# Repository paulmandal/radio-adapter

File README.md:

# Radio Adapter Board
Adapter board to connect a Yaesu VX-8DR with a Garmin GPSmap64 and various .mil microphones

# Requirements

- [Arduino](https://www.arduino.cc/en/Main/Software)
- [Eagle](https://www.autodesk.com/products/eagle/free-download)
- You must copy `ucontroller-code/platform.local.txt` to your `$ARDUINO_HOME/hardware/arduino/avr` directory to enable printf formatting of floats

# Table of Contents

| Directory | Contents |
|---|----|
| ucontroller-code | Arduino sketch to translate Garmin GPS NMEA sentences into the fixed-length that the Yaesu VX-8DR expects |
| circuit-board | Eagle circuit diagrams and PCB layouts for the adapter board |
| dev-tools | Various Python scripts that were useful during development |

# Important Note

The ATmega328p chips I got needed to have their fuses set, there is a script `set-fuses.sh` that will do this for you.  You may need to change the programmer from `usbtiny` to whatever you have on hand.

# References

This project borrows heavily from these sources:

[Reverse Engineering the Yaesu VX-8DR GPS Interface](http://lingnik.com/2013/02/09/reverse-engineering-yaesu-vx-8dr-gps-interface.html)

[Dynamic microphone to electret microphone input](http://www.epanorama.net/circuits/dynamic_to_electretinput.html)

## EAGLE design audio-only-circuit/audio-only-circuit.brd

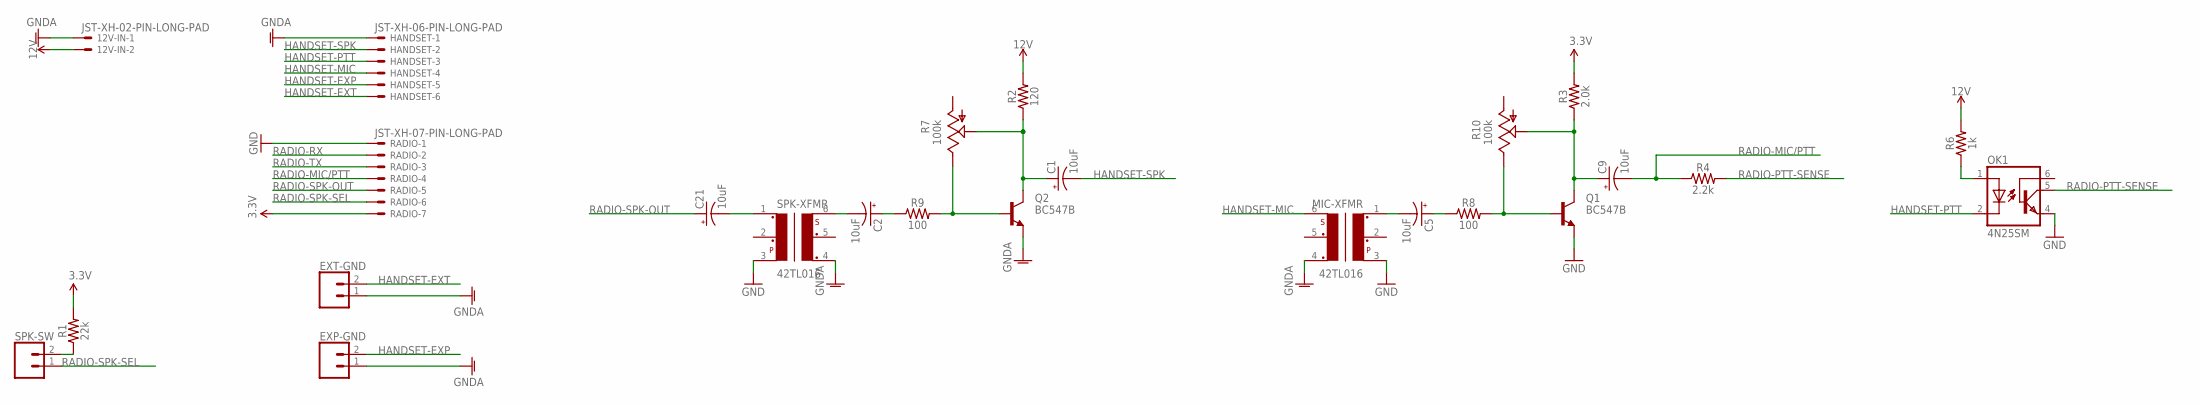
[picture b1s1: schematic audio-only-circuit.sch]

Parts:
12V-IN: JST-XH-02-PIN-LONG-PAD; JST-XH-02-PACKAGE-LONG-PAD
C1, C2, C5, C9, C21: 10uF; E2,5-5
EXP-GND: CONN_02; 1X02
EXT-GND: CONN_02; 1X02
HANDSET: JST-XH-06-PIN-LONG-PAD; JST-XH-06-PACKAGE-LONG-PAD
MIC-XFMR: 42TL016; 42TL
OK1: 4N25SM; DIL6-SMD
Q1, Q2: BC547B; TO92
R1: 22k; 0603
R2: 120; 0603
R3: 2.0k; 0603
R4: 2.2k; 0603
R6: 1k; 0603
R7, R10: 100k; S64W
R8, R9: 100; 0603
RADIO: JST-XH-07-PIN-LONG-PAD; JST-XH-07-PACKAGE-LONG-PAD
SPK-SW: CONN_02; 1X02
SPK-XFMR: 42TL016; 42TL

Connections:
3.3V: R1.2, R3.2, RADIO.7
12V: 12V-IN.2, R2.2, R6.2
GND: MIC-XFMR.3, OK1.4 (EMI), Q1.1 (E), RADIO.1, SPK-XFMR.3
GNDA: 12V-IN.1, EXP-GND.1, EXT-GND.1, HANDSET.1, MIC-XFMR.4, Q2.1 (E), SPK-XFMR.4
HANDSET-EXP: EXP-GND.2, HANDSET.5
HANDSET-EXT: EXT-GND.2, HANDSET.6
HANDSET-MIC: HANDSET.4, MIC-XFMR.6
HANDSET-PTT: HANDSET.3, OK1.2 (C)
HANDSET-SPK: C1.-, HANDSET.2
unnamed: C2.-, SPK-XFMR.6
unnamed: C9.+, Q1.3 (C), R3.1, R10.S
unnamed: Q1.2 (B), R8.2, R10.E
unnamed: Q2.2 (B), R7.E, R9.2
unnamed: C21.-, SPK-XFMR.1
unnamed: C5.-, MIC-XFMR.1
unnamed: C5.+, R8.1
unnamed: OK1.1 (A), R6.1
unnamed: C2.+, R9.1
unnamed: R1.1, SPK-SW.2
RADIO-MIC/PTT: C9.-, R4.1, RADIO.4
RADIO-PTT-SENSE: OK1.5 (COL), R4.2
RADIO-RX: RADIO.2
RADIO-SPK-OUT: C21.+, RADIO.5
RADIO-SPK-SEL: RADIO.6, SPK-SW.1
RADIO-TX: RADIO.3
SPKAMP: C1.+, Q2.3 (C), R2.1, R7.S

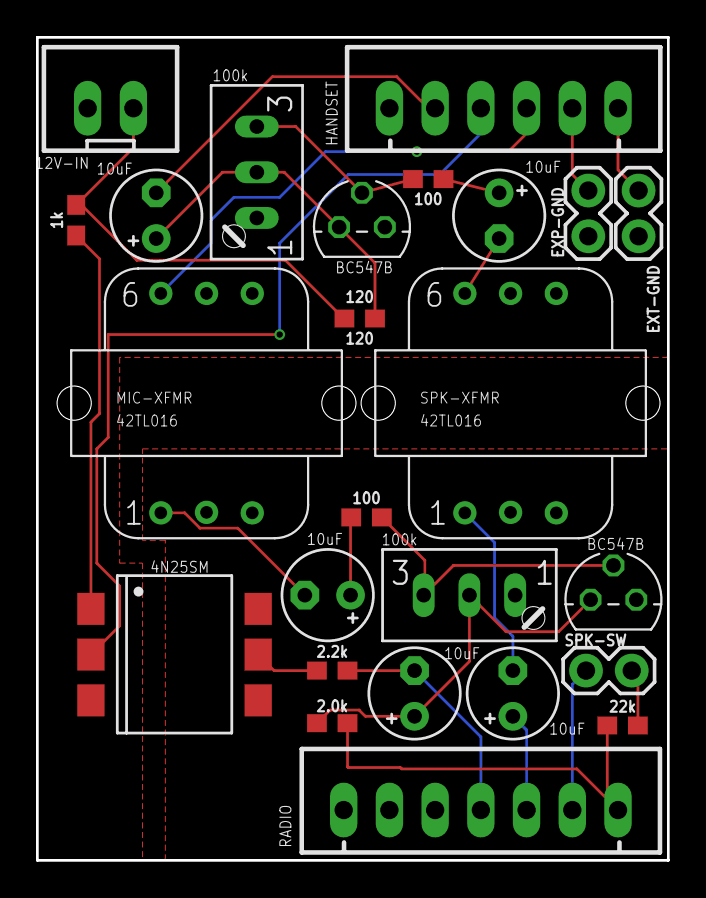
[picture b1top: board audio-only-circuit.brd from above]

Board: 2 copper layers, 35.1 x 45.7 mm, 25 parts (0 on the bottom side), 24 nets.

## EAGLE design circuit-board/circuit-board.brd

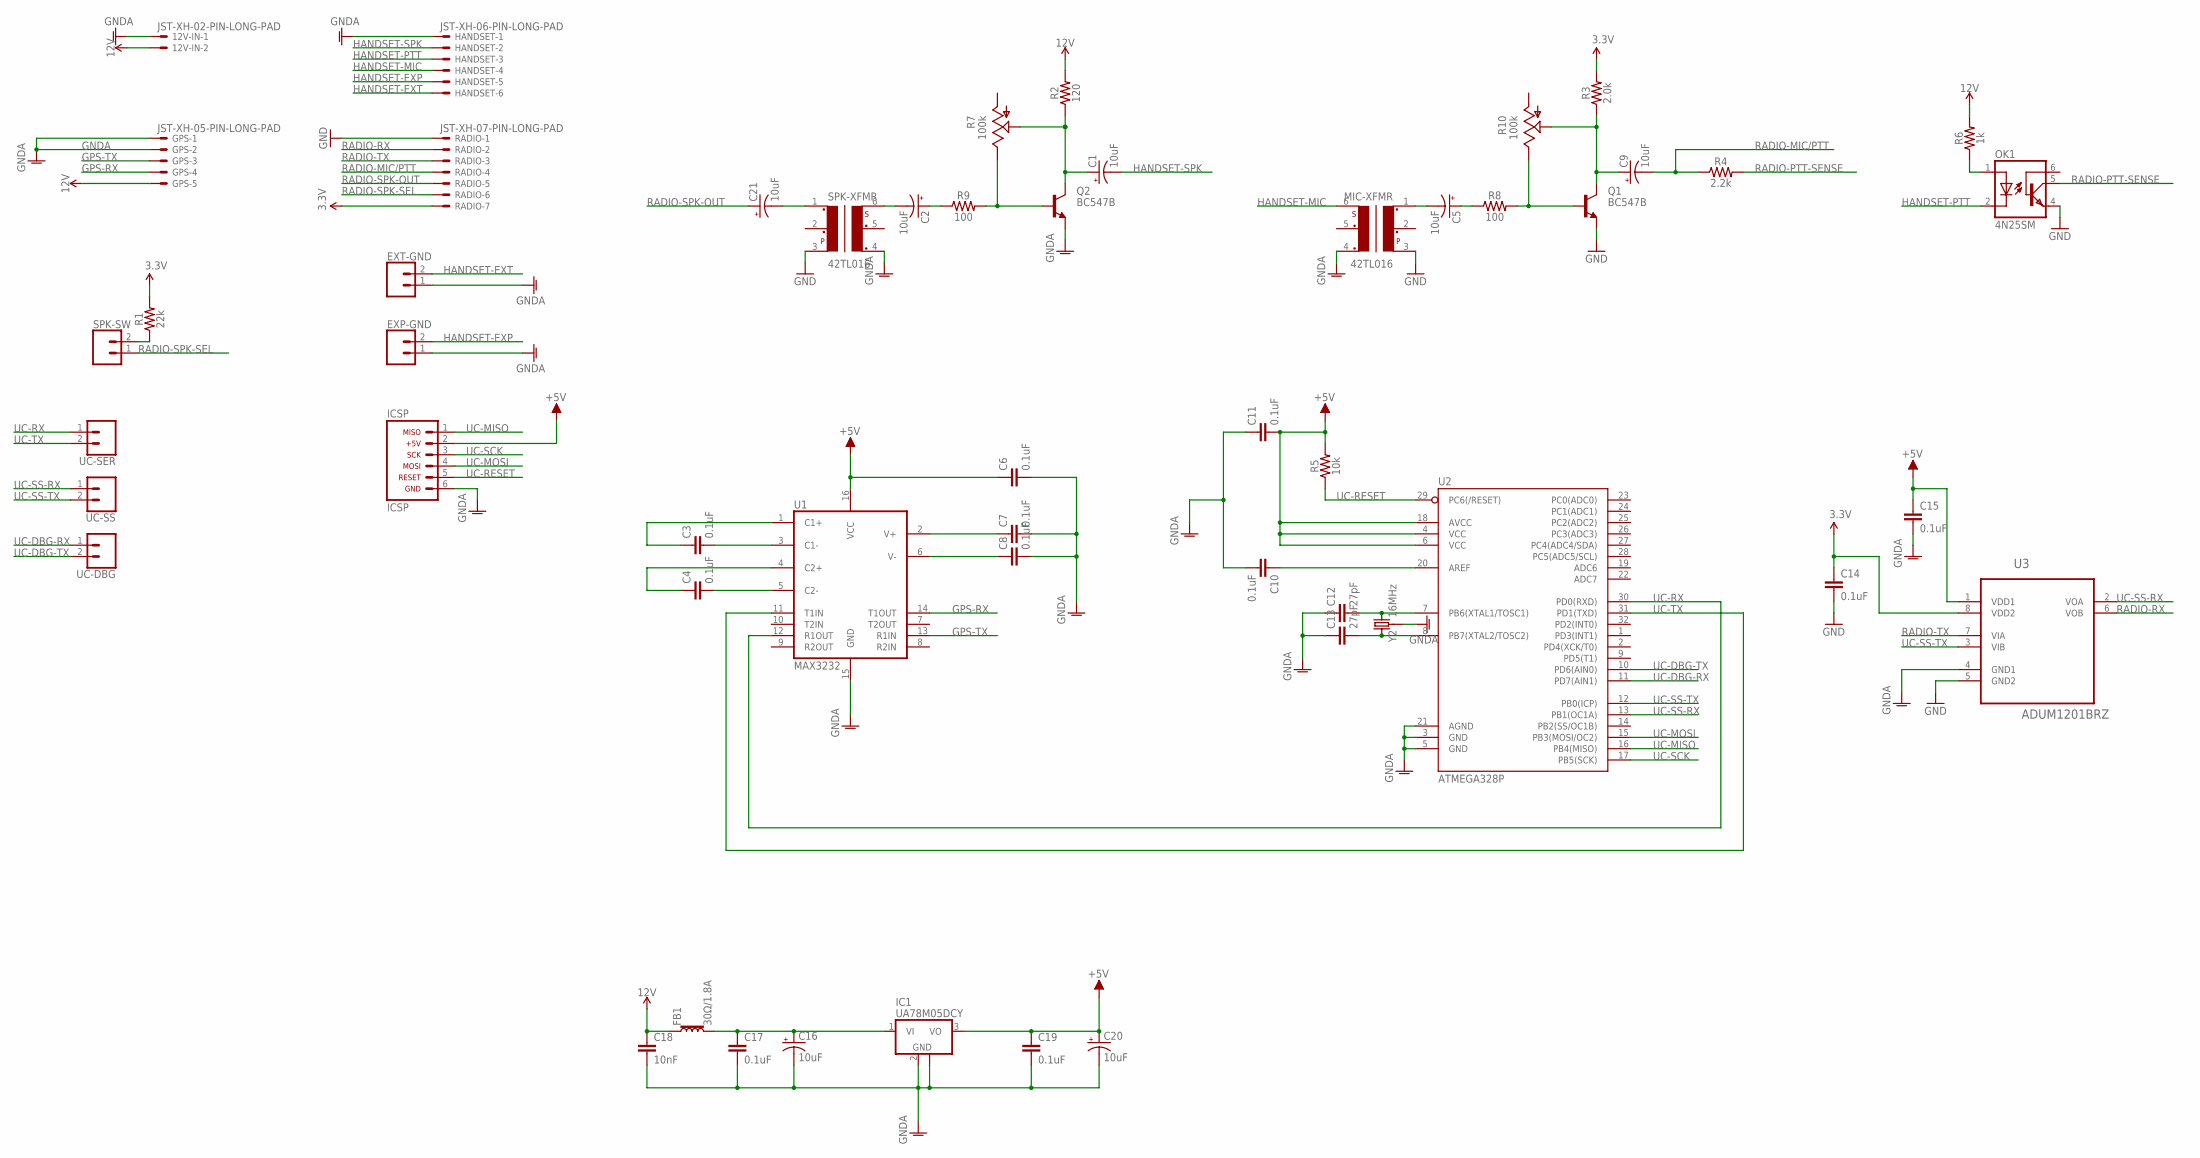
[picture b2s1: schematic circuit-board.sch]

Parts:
12V-IN: JST-XH-02-PIN-LONG-PAD; JST-XH-02-PACKAGE-LONG-PAD
C1, C2, C5, C9, C16, C20, C21: 10uF; E2,5-5
C3, C4, C6, C7, C8, C10, C11, C14, C15, C17, C19: 0.1uF; 0603
C12, C13: 27pF; 0603
C18: 10nF; 0603
EXP-GND: CONN_02; 1X02
EXT-GND: CONN_02; 1X02
FB1: 30Ω/1.8A; 0603
GPS: JST-XH-05-PIN-LONG-PAD; JST-XH-05-PACKAGE-LONG-PAD
HANDSET: JST-XH-06-PIN-LONG-PAD; JST-XH-06-PACKAGE-LONG-PAD
IC1: UA78M05DCY; SOT223
ICSP: ARDUINO_CONN-ICSP; CONN-2X03
MIC-XFMR: 42TL016; 42TL
OK1: 4N25SM; DIL6-SMD
Q1, Q2: BC547B; TO92
R1: 22k; 0603
R2: 120; 0603
R3: 2.0k; 0603
R4: 2.2k; 0603
R5: 10k; 0603
R6: 1k; 0603
R7, R10: 100k; S64W
R8, R9: 100; 0603
RADIO: JST-XH-07-PIN-LONG-PAD; JST-XH-07-PACKAGE-LONG-PAD
SPK-SW: CONN_02; 1X02
SPK-XFMR: 42TL016; 42TL
U1: MAX3232; SO16
U2: ATMEGA328P; TQFP32-08
U3: ADUM1201BRZ; SOIC127P600X175-8N
UC-DBG: CONN_02; 1X02
UC-SER: CONN_02; 1X02
UC-SS: CONN_02; 1X02
Y2: 16MHz; CRYSTAL-SMD-3.2X2.5MM

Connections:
3.3V: C14.1, R1.2, R3.2, RADIO.7, U3.8 (VDD2)
12V: 12V-IN.2, C18.1, FB1.1, GPS.5, R2.2, R6.2
+5V: C6.1, C11.2, C15.1, C19.1, C20.+, IC1.3 (VO), ICSP.2, R5.2, U1.16 (VCC), U2.4 (VCC), U2.6 (VCC), U2.18 (AVCC), U3.1 (VDD1)
GND: C14.2, MIC-XFMR.3, OK1.4 (EMI), Q1.1 (E), RADIO.1, SPK-XFMR.3, U3.5 (GND2)
GNDA: 12V-IN.1, C6.2, C7.2, C8.2, C10.2, C11.1, C12.1, C13.1, C15.2, C16.-, C17.2, C18.2, C19.2, C20.-, EXP-GND.1, EXT-GND.1, GPS.1, GPS.2, HANDSET.1, IC1.2 (GND), IC1.4 (GND), ICSP.6, MIC-XFMR.4, Q2.1 (E), SPK-XFMR.4, U1.15 (GND), U2.3 (GND), U2.5 (GND), U2.21 (AGND), U3.4 (GND1), Y2.2 (3), Y2.4 (3)
GPS-RX: GPS.4, U1.14 (T1OUT)
GPS-TX: GPS.3, U1.13 (R1IN)
HANDSET-EXP: EXP-GND.2, HANDSET.5
HANDSET-EXT: EXT-GND.2, HANDSET.6
HANDSET-MIC: HANDSET.4, MIC-XFMR.6
HANDSET-PTT: HANDSET.3, OK1.2 (C)
HANDSET-SPK: C1.-, HANDSET.2
unnamed: C16.+, C17.1, FB1.2, IC1.1 (VI)
unnamed: C2.-, SPK-XFMR.6
unnamed: C9.+, Q1.3 (C), R3.1, R10.S
unnamed: Q1.2 (B), R8.2, R10.E
unnamed: Q2.2 (B), R7.E, R9.2
unnamed: C21.-, SPK-XFMR.1
unnamed: C5.-, MIC-XFMR.1
unnamed: C5.+, R8.1
unnamed: OK1.1 (A), R6.1
unnamed: C2.+, R9.1
unnamed: R1.1, SPK-SW.2
unnamed: C3.2, U1.3 (C1-)
unnamed: C3.1, U1.1 (C1+)
unnamed: C4.2, U1.5 (C2-)
unnamed: C4.1, U1.4 (C2+)
unnamed: C7.1, U1.2 (V+)
unnamed: C8.1, U1.6 (V-)
unnamed: C10.1, U2.20 (AREF)
unnamed: C12.2, U2.7 (PB6(XTAL1/TOSC1)), Y2.3 (2)
unnamed: C13.2, U2.8 (PB7(XTAL2/TOSC2)), Y2.1
RADIO-MIC/PTT: C9.-, R4.1, RADIO.4
RADIO-PTT-SENSE: OK1.5 (COL), R4.2
RADIO-RX: RADIO.2, U3.6 (VOB)
RADIO-SPK-OUT: C21.+, RADIO.5
RADIO-SPK-SEL: RADIO.6, SPK-SW.1
RADIO-TX: RADIO.3, U3.7 (VIA)
SPKAMP: C1.+, Q2.3 (C), R2.1, R7.S
UC-DBG-RX: U2.11 (PD7(AIN1)), UC-DBG.1
UC-DBG-TX: U2.10 (PD6(AIN0)), UC-DBG.2
UC-MISO: ICSP.1, U2.16 (PB4(MISO))
UC-MOSI: ICSP.4, U2.15 (PB3(MOSI/OC2))
UC-RESET: ICSP.5, R5.1, U2.29 (PC6(/RESET))
UC-RX: U1.12 (R1OUT), U2.30 (PD0(RXD)), UC-SER.1
UC-SCK: ICSP.3, U2.17 (PB5(SCK))
UC-SS-RX: U2.13 (PB1(OC1A)), U3.2 (VOA), UC-SS.1
UC-SS-TX: U2.12 (PB0(ICP)), U3.3 (VIB), UC-SS.2
UC-TX: U1.11 (T1IN), U2.31 (PD1(TXD)), UC-SER.2

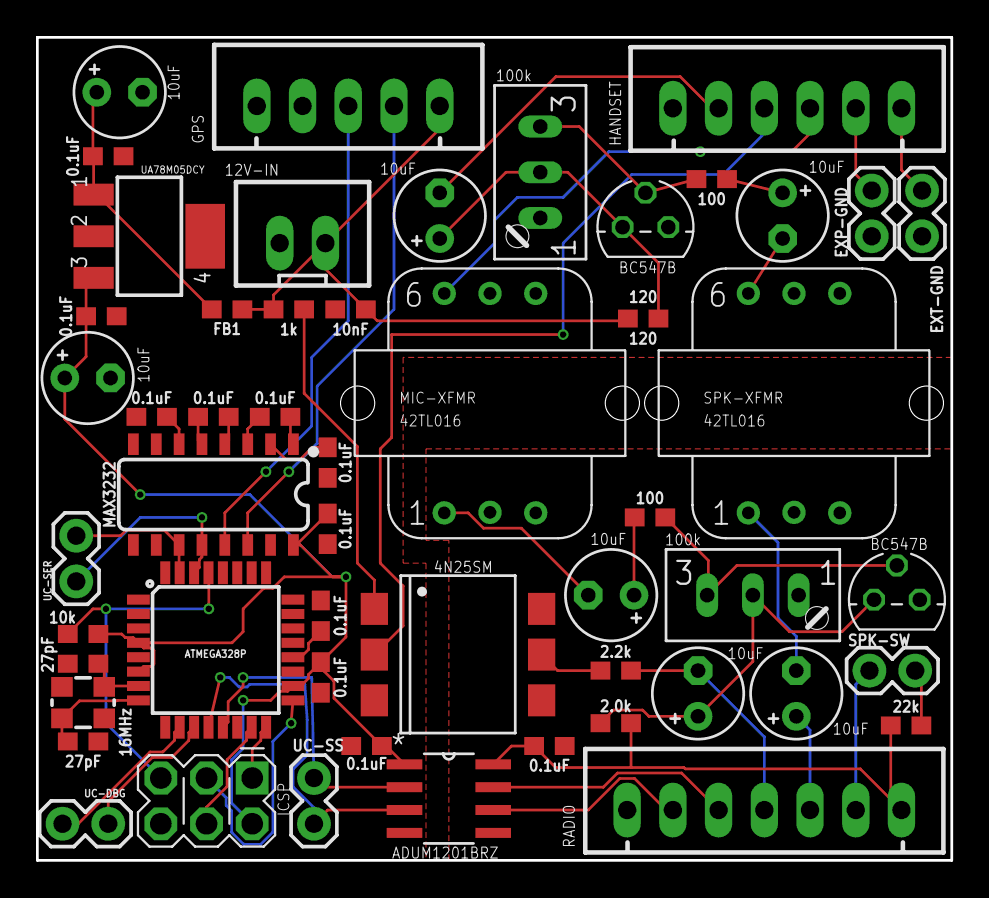
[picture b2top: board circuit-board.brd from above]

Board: 2 copper layers, 50.8 x 45.7 mm, 53 parts (0 on the bottom side), 49 nets.

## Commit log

2018-03-18 Circuit schematic finalized, laying out PCB now
2018-03-18 Added *.pro and *.job files to .gitignore
2018-03-18 Added basic GPS NMEA -> X8-DR NMEA translation microcontroller code
2018-03-18 Manually routed some connections
2018-03-18 Added voltage regulator, dropped some JSTs, relaid out board, rerouted
2018-03-18 Done for tonight, PCB laid out, need to verify ERC/DRC tomorrow
2018-03-18 This worked great with my USB soundcard but not at all with the radio, giving up on this approach -- a BC547 does the trick and eliminates a bunch of isolation and some battery usage
2018-03-18 Manually routed a few more lines
2018-03-18 Added 0 Ohm resistor to avoid renaming nets, finished initial PCB layout
2018-03-18 Board is final, sending to fab shop
2018-03-18 Super-final, extended ground plane near radio JST
2018-03-18 Added labels for JST header pins, synced up board+schematic resistor values
2018-03-18 Moved version message to bottom layer
2018-03-18 Added some debug output to vx8dr-basic.ino
2018-03-18 Almost finished circuit board schematic
2018-03-18 Added .gitignore
2018-03-18 Added debug output to uController code
2018-04-01 Improved README, added picture of finished PCB, reorganized directory structure
2018-04-01 Updated README image link to master branch
2018-12-01 Update scratchpad.txt with V2 feature list Create v2-scratch.sch to prototype V2 board implementation - Add isolation transformers for mic/spk on handset - Add optoisolation for PTT on handset - Add 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
2018-12-02 Clean up circuit diagrams, prep for prototype
2018-12-03 Start new circuit board, fix some small circuit design issues
2018-12-06 Lay out circuit board, preliminary
2018-12-07 Minimize V2 board layout
2018-12-07 Add ground planes, routes to V2 board
2018-12-08 Route V2 board manually, fix up silkscreen
2018-12-08 Tweak some resistor values in V2 board based on breadboard testing. Add small input resistors on both amplifying transistors -- this cleans up the mic signal a lot!
2018-12-08 Route new connections for amplifier input resistors
2018-12-08 Tent vias by adjusting viaStopLimit
2018-12-08 Eliminate overlapping parts in V2 board layout
2018-12-16 Fix placement of design/version text on silkscreen -- too bad this already went to the fab :/
2018-12-16 Rename vx8dr-basic/vx8dr-basic -> ucontroller-code/message-transformer.ino
2018-12-16 Renamed message-transformer.ino -> ucontroller-code.ino
2018-12-17 Add comments to read-gps-msgs.py, create test-ucontroller.py
2018-12-17 Basic implementation for test-ucontroller.py, update README.md
2018-12-17 Improve test-ucontroller.py, fix some small bugs, improve output
2018-12-17 Strip newlines from output in test-ucontroller.py, fix extra newlines in ucontroller-code.ino
2018-12-17 Switch to NeoSWSerial for serial handling, fix an issue where software serial was writing to both ports
2018-12-17 Switch to NeoHWSerial for hardware serial input
2018-12-17 Add MessageBuffer class -- this is in preparation to switching to an interrupt-driven model for serial input processing
2018-12-17 Switch to an interrupt-driven model for serial input consumption
2018-12-17 Start switching to a class-based solution for message transformation -- class has various configurable options for padding, prefix/suffix, static fields
2018-12-17 Got class version of message transform working, need to do code cleanup
2018-12-17 Improve dev-tools by setting character encoding to ASCII, adding template messages from the FGPS-2 module c/o Taylor KG7BBG, and adding an option to compare radio-adapter responses with expected resp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
2018-12-17 Convert leftPadNumber() to use pointers to strings instead of String
2018-12-18 Switch MessageTransform to use pointers to strings instead of String, rename some structs, add skeletons for NMEA message configs, add mapping for NMEA->transform
2018-12-18 Add the ability to disable debugging output using compiler directives
2018-12-18 Fix handling of GPGLL NMEA messages
2018-12-18 Add rightPadNumber()
2018-12-18 Add dropping and right-hand padding of fields
2018-12-18 MessageTransform class got too complicated, let's use sprintf instead
2018-12-18 Implemented GGA NMEA message transform, added platform.local.txt to enable printf float formatting
2018-12-18 Implement GGL message transform, added debug serials temporarily
2018-12-18 Add handling for RMC NMEA messages
2018-12-18 Add handling for VTG NMEA messages
2018-12-18 Remove reserved words from message transformation functions
2018-12-18 Add handling for unknown fields to message transformer functions
2018-12-18 Add small script to test GPS integration
2018-12-18 Remove unused string_manip.h and string_manip.cpp files
2018-12-18 Remove debug serial from message transformation functions
2018-12-18 Add newlines to NMEA messages, remove unused header files
2018-12-18 Reduce and/or remove timeouts in test scripts
2018-12-18 Condense parsing of NMEA messages in transform functions
2018-12-26 Add shell script to set uController fuses, add note to README.md about it
2018-12-26 Fix an issue where empty messages would be sent to the radio when a mapping to a message transform could not be found
2018-12-26 Disable debug port for live testing
2019-01-06 Switched 100/120 ohm resistors in audio amp circuit for 1k resistors -- noise almost eliminated, though serial noise remains.. will need to split up ground planes to clear that up
2019-01-06 Update message transform to not allocate memory for an output message if GPS fix it not found yet, instead we return NULL and check for NULL in the main loop
2019-01-06 Add list of V3 improvements
2019-01-07 Update README.md with new build pictures
2019-07-14 Updated resistor values on adapter board to be consistent with what I ended up building
2019-07-14 Create a new version of the board for audio-only applications (i.e. no GPS)
2019-07-14 Updated BOM for v1.0 audio-only board

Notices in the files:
parts and their libraries:
SparkFun-Connectors: Licensing: Creative Commons ShareAlike 4.0 International - https://creativecommons.org/licenses/by-sa/4.0
SparkFun: Licensing: CC v3.0 Share-Alike You are welcome to use this library for commercial purposes.
supply4: Copyright (C) 2007, Bob Starr
